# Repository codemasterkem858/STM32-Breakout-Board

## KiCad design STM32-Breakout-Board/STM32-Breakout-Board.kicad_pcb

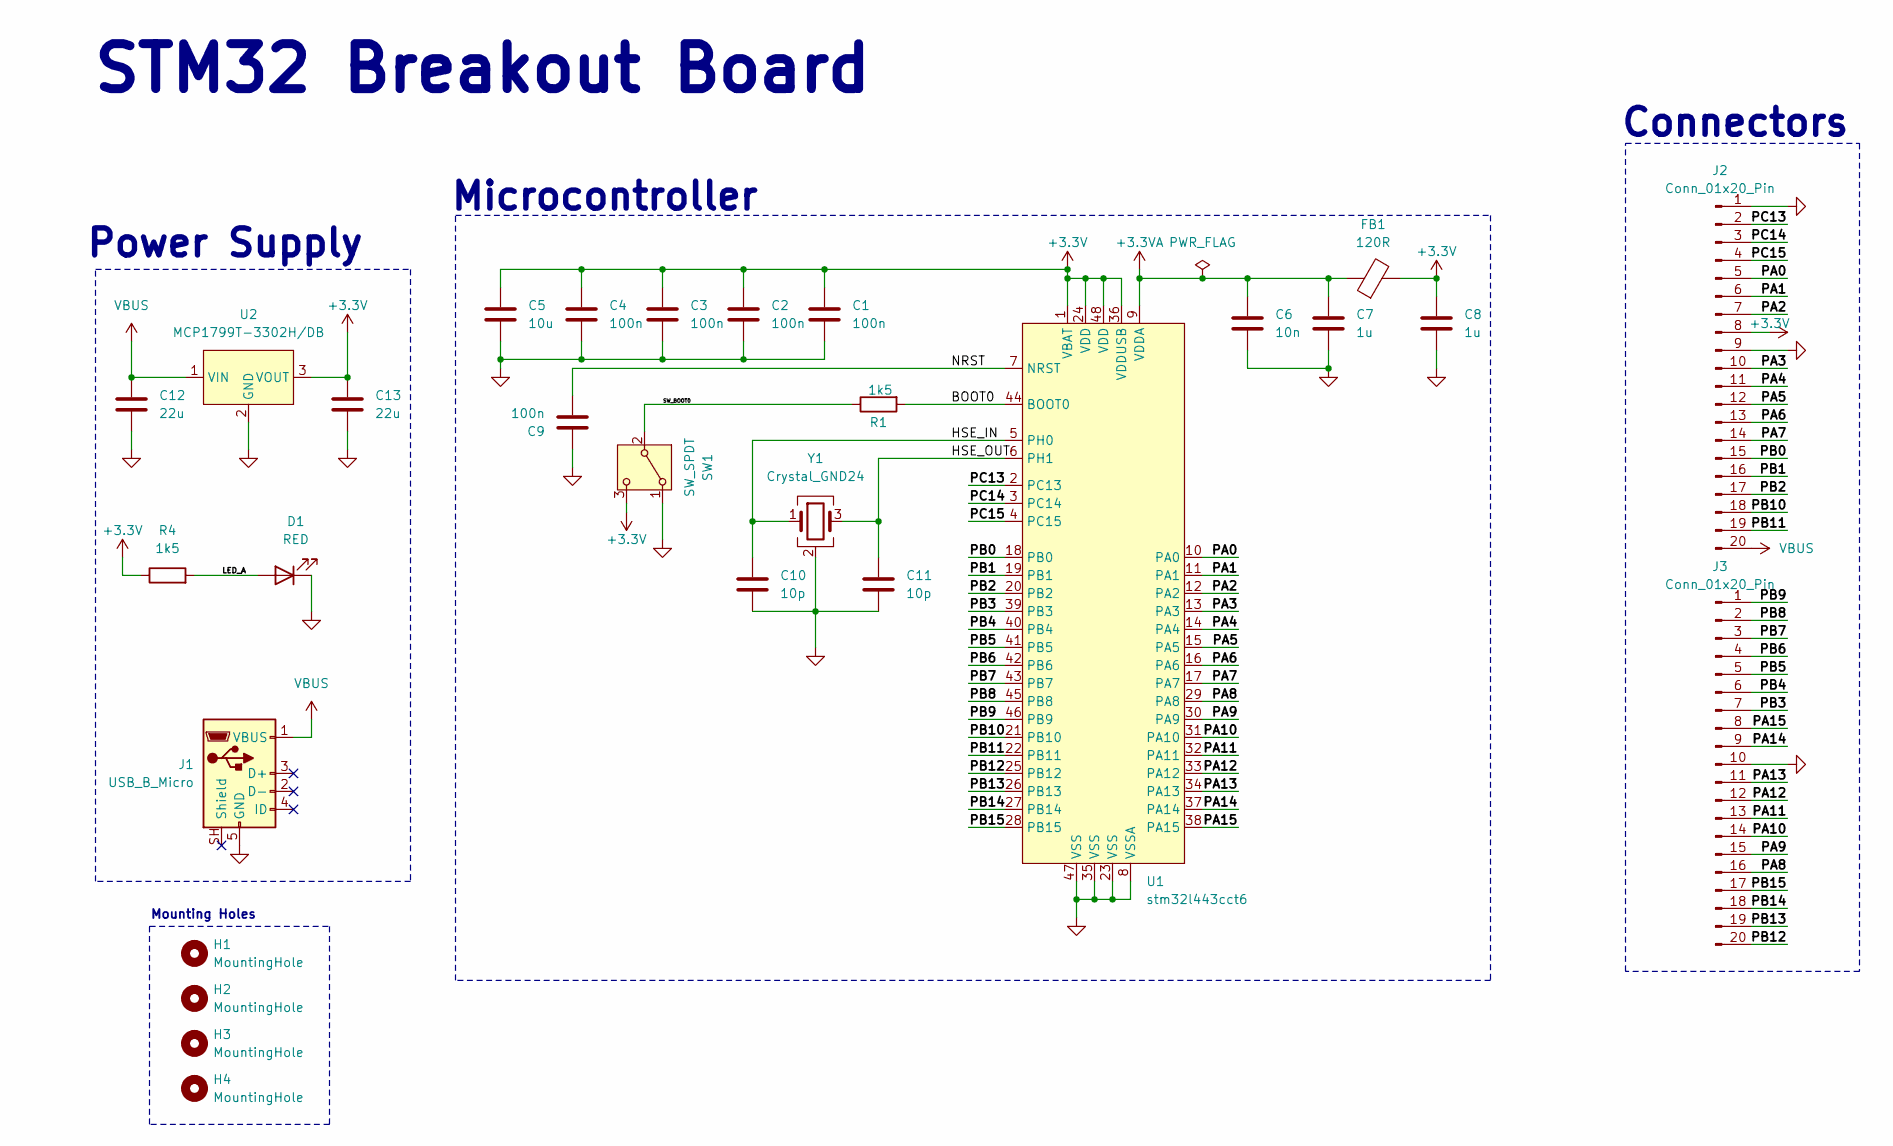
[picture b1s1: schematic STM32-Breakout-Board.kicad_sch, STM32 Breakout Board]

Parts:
C1, C2, C3, C4, C9: 100n; C_0402_1005Metric; Part Number 04025C104JAT2A
C5: 10u; C_0805_2012Metric; Part Number CGA4J1X7R0J106K125AC
C6: 10n; C_0402_1005Metric; Part Number KAM05AR71C103JH
C7, C8: 1u; C_0603_1608Metric; Part Number KGM15BR71C105JT
C10, C11: 10p; C_0402_1005Metric; Part Number KGM05ACG1H100JH
C12, C13: 22u; C_0805_2012Metric; Part Number KGM21AR51C226KU
D1: RED; LED_0603_1608Metric; Part Number TLMS1000-GS15
FB1: 120R; L_0603_1608Metric; Part Number BLM18BD121SH1D
H1, H2, H3, H4: MountingHole; MountingHole_2.5mm
J1: USB_B_Micro; USB_Micro-B_Wuerth_629105150521; Part Number 629105150521
J2, J3: Conn_01x20_Pin; PinHeader_1x20_P2.54mm_Vertical; Part Number M20-9992046
R1, R4: 1k5; R_0402_1005Metric; Part Number CQ02WGJ0152TCE
SW1: SW_SPDT; SW_SPDT_PCM12; Part Number COM-09609
U1: stm32l443cct6; LQFP48; Part Number stm32l443cct6
U2: MCP1799T-3302H/DB; SOT-223 b; Part Number MCP1799-5002H/DB
Y1: Crystal_GND24; Crystal_SMD_3225-4Pin_3.2x2.5mm; Part Number CX3225CA12000F0KFQCC

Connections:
+3.3V: C1.1, C2.1, C3.1, C4.1, C5.1, C8.1, C13.1, FB1.2, J2.8, R4.1, SW1.3 (C), U1.1 (VBAT), U1.24 (VDD), U1.36 (VDDUSB), U1.48 (VDD), U2.3 (VOUT); also elsewhere on the board
+3.3VA: C6.1, C7.1, FB1.1, U1.9 (VDDA)
/BOOT0: R1.2, U1.44 (BOOT0)
/HSE_IN: C10.1, U1.5 (PH0), Y1.1
/HSE_OUT: C11.1, U1.6 (PH1), Y1.3
/LED_A: D1.2 (A), R4.2
/NRST: C9.2, U1.7 (NRST)
/PA0: J2.5, U1.10 (PA0)
/PA1: J2.6, U1.11 (PA1)
/PA2: J2.7, U1.12 (PA2)
/PA3: J2.10, U1.13 (PA3)
/PA4: J2.11, U1.14 (PA4)
/PA5: J2.12, U1.15 (PA5)
/PA6: J2.13, U1.16 (PA6)
/PA7: J2.14, U1.17 (PA7)
/PA8: J3.16, U1.29 (PA8)
/PA9: J3.15, U1.30 (PA9)
/PA10: J3.14, U1.31 (PA10)
/PA11: J3.13, U1.32 (PA11)
/PA12: J3.12, U1.33 (PA12)
/PA13: J3.11, U1.34 (PA13)
/PA14: J3.9, U1.37 (PA14)
/PA15: J3.8, U1.38 (PA15)
/PB0: J2.15, U1.18 (PB0)
/PB1: J2.16, U1.19 (PB1)
/PB2: J2.17, U1.20 (PB2)
/PB3: J3.7, U1.39 (PB3)
/PB4: J3.6, U1.40 (PB4)
/PB5: J3.5, U1.41 (PB5)
/PB6: J3.4, U1.42 (PB6)
/PB7: J3.3, U1.43 (PB7)
/PB8: J3.2, U1.45 (PB8)
/PB9: J3.1, U1.46 (PB9)
/PB10: J2.18, U1.21 (PB10)
/PB11: J2.19, U1.22 (PB11)
/PB12: J3.20, U1.25 (PB12)
/PB13: J3.19, U1.26 (PB13)
/PB14: J3.18, U1.27 (PB14)
/PB15: J3.17, U1.28 (PB15)
/PC13: J2.2, U1.2 (PC13)
/PC14: J2.3, U1.3 (PC14)
/PC15: J2.4, U1.4 (PC15)
/SW_BOOT0: R1.1, SW1.2 (B); also elsewhere on the board
GND: C1.2, C2.2, C3.2, C4.2, C5.2, C6.2, C7.2, C8.2, C9.1, C10.2, C11.2, C12.2, C13.2, D1.1 (K), J1.5 (GND), J2.1, J2.9, J3.10, SW1.1 (A), U1.8 (VSSA), U1.23 (VSS), U1.35 (VSS), U1.47 (VSS), U2.2 (GND), Y1.2 (G), Y1.4 (G); also elsewhere on the board
VBUS: C12.1, J1.1 (VBUS), J2.20, U2.1 (VIN); also elsewhere on the board

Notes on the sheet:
Mounting Holes
STM32 Breakout Board
Connectors
Power Supply
Microcontroller

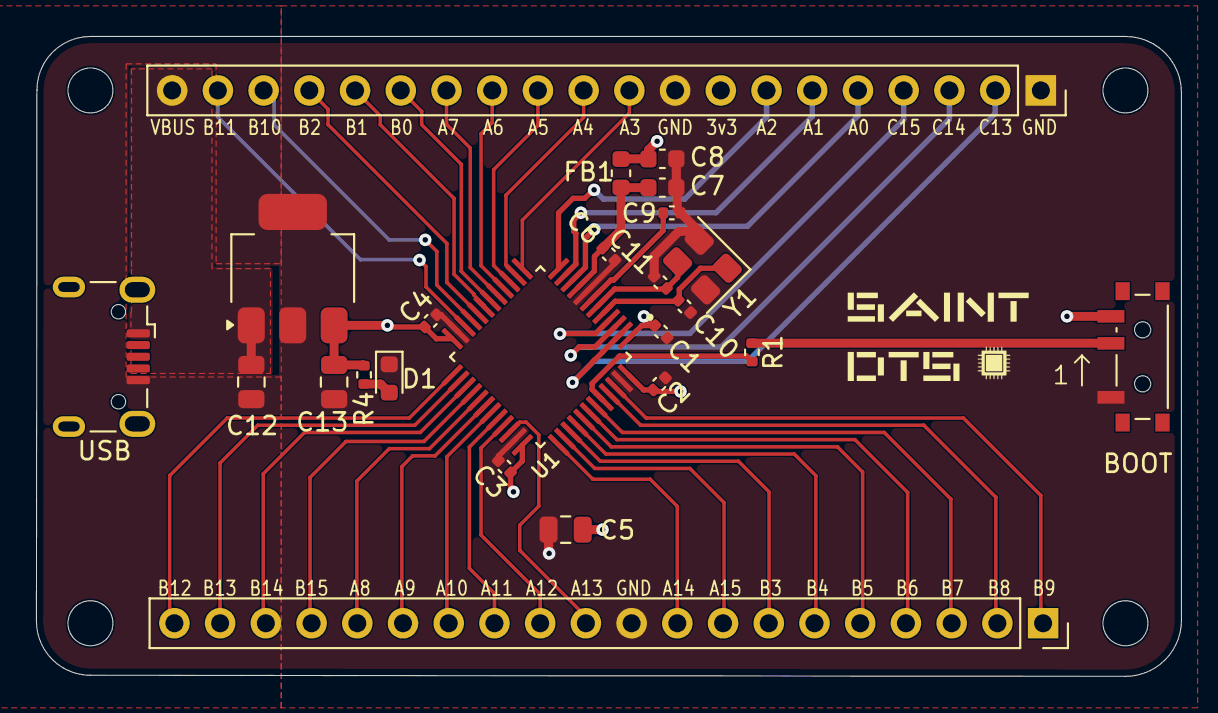
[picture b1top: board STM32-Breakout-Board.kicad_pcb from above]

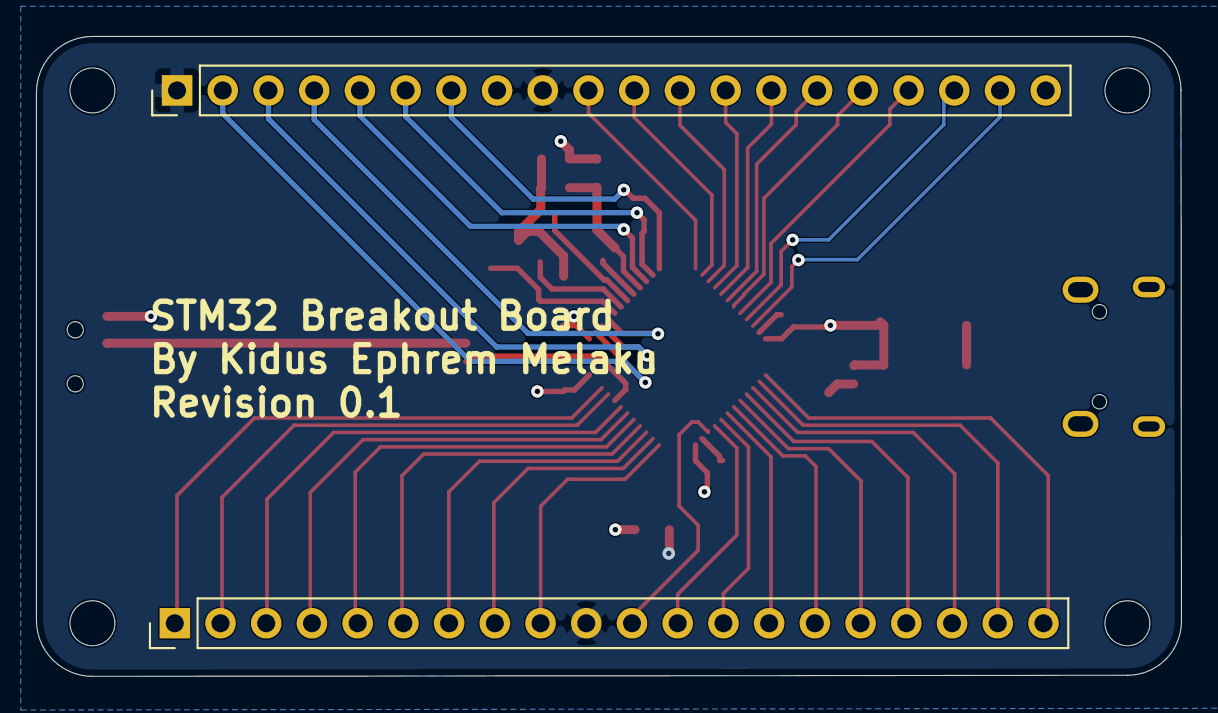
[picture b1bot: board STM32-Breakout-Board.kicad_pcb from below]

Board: 4 copper layers, 63.6 x 35.6 mm, 28 parts (2 on the bottom side), 45 nets.

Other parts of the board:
BOOT: SW_SPDT; SW_SPDT_PCM12
USB: USB_B_Micro; USB_Micro-B_Wuerth_629105150521

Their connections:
+3.3V: BOOT.3 (C); also elsewhere on the board
/SW_BOOT0: BOOT.2 (B); also elsewhere on the board
GND: BOOT.1 (A), USB.5 (GND); also elsewhere on the board
VBUS: USB.1 (VBUS); also elsewhere on the board
